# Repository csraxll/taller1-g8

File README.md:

# taller1-g8
Repositorio del proyecto del Grupo 8 para la materia Taller de Proyecto 1 - Ingeniería en Computación - UNLP

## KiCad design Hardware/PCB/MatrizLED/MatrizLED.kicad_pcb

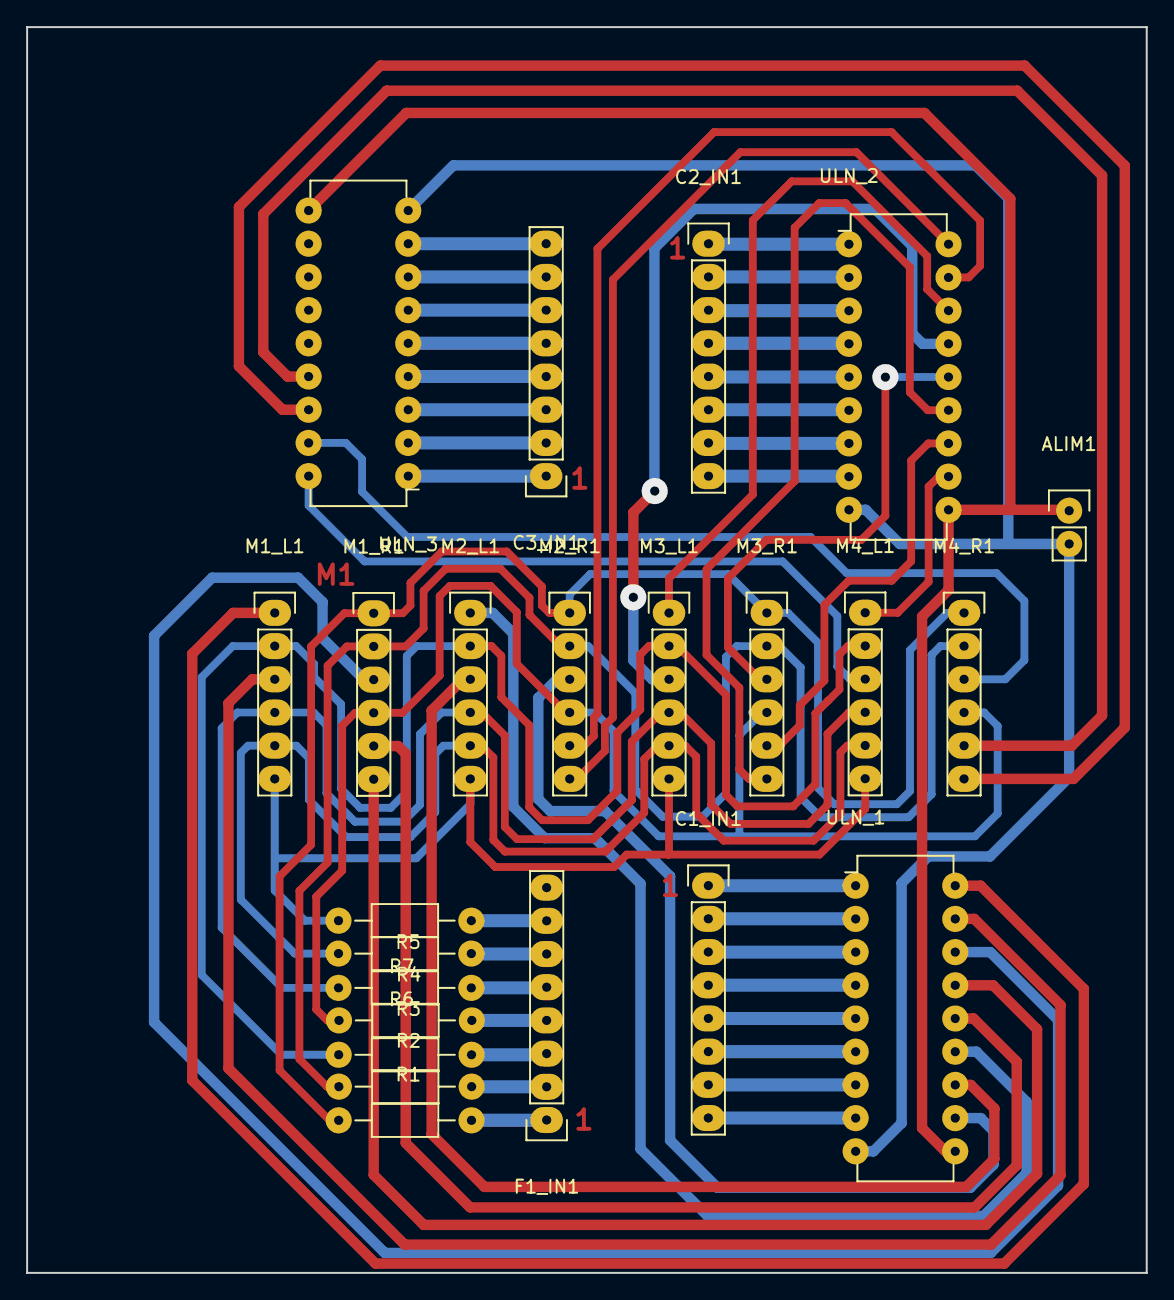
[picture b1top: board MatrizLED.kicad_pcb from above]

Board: 2 copper layers, 85.7 x 95.3 mm, 23 parts (0 on the bottom side), 60 nets.

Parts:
ALIM1: CONN_01X02; Pin_Header_Straight_1x02
C1_IN1, C2_IN1, C3_IN1: CONN_01X08; Pin_Header_Straight_1x08
F1_IN1: CONN_01X08; Pin_Header_Straight_1x08
M1_L1, M1_R1, M2_L1, M2_R1, M3_L1, M3_R1, M4_L1, M4_R1: CONN_01X06; Pin_Header_Straight_1x06
R1, R2, R3, R4, R5, R6, R7: R; Resistor_Horizontal_RM10mm
ULN_1, ULN_2, ULN_3: ULN2803; DIP-18_W7.62mm

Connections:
GND: ALIM1.2, ULN_1.9, ULN_2.9, ULN_3.9
unnamed: C1_IN1.1, ULN_1.1
unnamed: C1_IN1.2, ULN_1.2
unnamed: C1_IN1.3, ULN_1.3
unnamed: C1_IN1.4, ULN_1.4
unnamed: C1_IN1.5, ULN_1.5
unnamed: C1_IN1.6, ULN_1.6
unnamed: C1_IN1.7, ULN_1.7
unnamed: C1_IN1.8, ULN_1.8
unnamed: C2_IN1.1, ULN_2.1
unnamed: C2_IN1.2, ULN_2.2
unnamed: C2_IN1.3, ULN_2.3
unnamed: C2_IN1.4, ULN_2.4
unnamed: C2_IN1.5, ULN_2.5
unnamed: C2_IN1.6, ULN_2.6
unnamed: C2_IN1.7, ULN_2.7
unnamed: C2_IN1.8, ULN_2.8
unnamed: C3_IN1.1, ULN_3.1
unnamed: C3_IN1.2, ULN_3.2
unnamed: C3_IN1.3, ULN_3.3
unnamed: C3_IN1.4, ULN_3.4
unnamed: C3_IN1.5, ULN_3.5
unnamed: C3_IN1.6, ULN_3.6
unnamed: C3_IN1.7, ULN_3.7
unnamed: C3_IN1.8, ULN_3.8
unnamed: F1_IN1.1, R1.2
unnamed: F1_IN1.2, R2.2
unnamed: F1_IN1.3, R3.2
unnamed: F1_IN1.4, R4.2
unnamed: F1_IN1.5, R5.2
unnamed: F1_IN1.6, R6.1
unnamed: F1_IN1.7, R7.1
unnamed: M1_L1.1, ULN_1.18
unnamed: M1_L1.2, M2_L1.2, M3_L1.2, M4_L1.2, R3.1
unnamed: M1_L1.3, ULN_1.17
unnamed: M1_L1.4, M2_L1.4, M3_L1.4, M4_L1.4, R5.1
unnamed: M1_L1.5, M2_L1.5, M3_L1.5, M4_L1.5, R6.2
unnamed: M1_L1.6, M2_L1.6, M3_L1.6, M4_L1.6, R7.2
unnamed: M1_R1.1, M2_R1.1, M3_R1.1, M4_R1.1, R1.1
unnamed: M1_R1.2, M2_R1.2, M3_R1.2, M4_R1.2, R2.1
unnamed: M1_R1.3, ULN_1.16
unnamed: M1_R1.4, M2_R1.4, M3_R1.4, M4_R1.4, R4.1
unnamed: M1_R1.5, ULN_1.14
unnamed: M1_R1.6, ULN_1.15
unnamed: M2_L1.1, ULN_1.13
unnamed: M2_L1.3, ULN_1.12
unnamed: M2_R1.3, ULN_1.11
unnamed: M2_R1.5, ULN_2.17
unnamed: M2_R1.6, ULN_2.18
unnamed: M3_L1.1, ULN_2.16
unnamed: M3_L1.3, ULN_2.15
unnamed: M3_R1.3, ULN_2.14
unnamed: M3_R1.5, ULN_2.12
unnamed: M3_R1.6, ULN_2.13
unnamed: M4_L1.1, ULN_2.11
unnamed: M4_L1.3, ULN_3.18
unnamed: M4_R1.3, ULN_3.17
unnamed: M4_R1.5, ULN_3.15
unnamed: M4_R1.6, ULN_3.16
VCC: ALIM1.1, ULN_1.10, ULN_2.10, ULN_3.10

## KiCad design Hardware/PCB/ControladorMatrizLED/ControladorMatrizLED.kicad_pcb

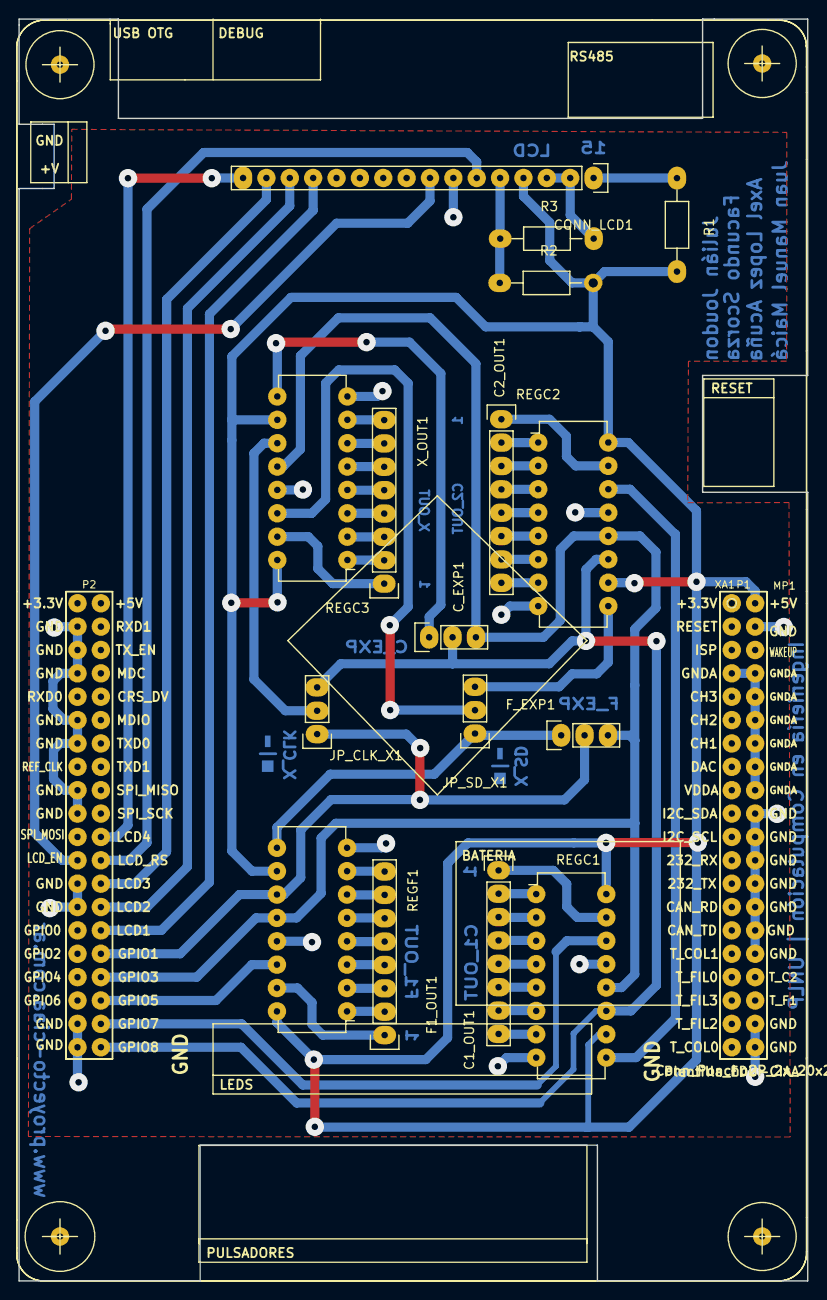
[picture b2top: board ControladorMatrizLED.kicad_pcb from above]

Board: 2 copper layers, 85.7 x 137.2 mm, 18 parts (0 on the bottom side), 54 nets.

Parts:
C1_OUT1, C2_OUT1: CONN_01X08; Socket_Strip_Straight_1x08
CONN_LCD1: CONN_01X16; Socket_Strip_Straight_1x16
C_EXP1: CONN_01X03; Socket_Strip_Straight_1x03
F1_OUT1: CONN_01X08; Socket_Strip_Straight_1x08
F_EXP1: CONN_01X03; Socket_Strip_Straight_1x03
JP_CLK_X1: CONN_01X03; Socket_Strip_Straight_1x03
JP_SD_X1: CONN_01X03; Socket_Strip_Straight_1x03
MP1: Plantilla_EDU-CIAA
R1, R2, R3: R; Resistor_Horizontal_RM10mm
REGC1, REGC2, REGC3: 74HC595; DIP-16_W7.62mm
REGF1: 74HC595; DIP-16_W7.62mm
XA1: Conn_Poncho2P_2x_20x2; poncho_grande
X_OUT1: CONN_01X08; Socket_Strip_Straight_1x08

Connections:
/Circuito Principal/GPIO1: F_EXP1.2, JP_CLK_X1.1, REGF1.11, XA1.72
/Circuito Principal/GPIO3: C_EXP1.3, F_EXP1.3, REGC1.12, REGC2.12, REGC3.12, REGF1.12, XA1.74
/Circuito Principal/GPIO5: REGF1.14, XA1.76
/Circuito Principal/GPIO7: REGC1.14, XA1.78
/Circuito Principal/GPIO8: C_EXP1.2, JP_CLK_X1.3, REGC1.11, REGC2.11, XA1.80
/Circuito Principal/LCD1: CONN_LCD1.13, XA1.70
/Circuito Principal/LCD2: CONN_LCD1.14, XA1.68
/Circuito Principal/LCD3: CONN_LCD1.15, XA1.66
/Circuito Principal/LCD4: CONN_LCD1.16, XA1.62
/Circuito Principal/LCD_EN: CONN_LCD1.8, XA1.63
/Circuito Principal/RS: CONN_LCD1.6, XA1.64
GND: CONN_LCD1.2, CONN_LCD1.3, CONN_LCD1.7, R3.2, REGC1.8, REGC1.13, REGC2.8, REGC2.13, REGC3.8, REGC3.13, REGF1.8, REGF1.13, XA1.4, XA1.20, XA1.22, XA1.24, XA1.26, XA1.28, XA1.30, XA1.32, XA1.38, XA1.40, XA1.43, XA1.45, XA1.47, XA1.51, XA1.53, XA1.57, XA1.59, XA1.65, XA1.67, XA1.77, XA1.79
GNDA: XA1.7, XA1.8, XA1.10, XA1.12, XA1.14, XA1.16, XA1.18
unnamed: C1_OUT1.1, REGC1.15
unnamed: C1_OUT1.2, REGC1.1
unnamed: C1_OUT1.3, REGC1.2
unnamed: C1_OUT1.4, REGC1.3
unnamed: C1_OUT1.5, REGC1.4
unnamed: C1_OUT1.6, REGC1.5
unnamed: C1_OUT1.7, REGC1.6
unnamed: C1_OUT1.8, REGC1.7
unnamed: C2_OUT1.1, REGC2.15
unnamed: C2_OUT1.2, REGC2.1
unnamed: C2_OUT1.3, REGC2.2
unnamed: C2_OUT1.4, REGC2.3
unnamed: C2_OUT1.5, REGC2.4
unnamed: C2_OUT1.6, REGC2.5
unnamed: C2_OUT1.7, REGC2.6
unnamed: C2_OUT1.8, REGC2.7
unnamed: CONN_LCD1.1, R1.1
unnamed: CONN_LCD1.5, R2.1, R3.1
unnamed: C_EXP1.1, REGC3.9
unnamed: F1_OUT1.1, REGF1.15
unnamed: F1_OUT1.2, REGF1.1
unnamed: F1_OUT1.3, REGF1.2
unnamed: F1_OUT1.4, REGF1.3
unnamed: F1_OUT1.5, REGF1.4
unnamed: F1_OUT1.6, REGF1.5
unnamed: F1_OUT1.7, REGF1.6
unnamed: F1_OUT1.8, REGF1.7
unnamed: F_EXP1.1, JP_SD_X1.1, REGF1.9
unnamed: JP_CLK_X1.2, REGC3.11
unnamed: JP_SD_X1.2, REGC3.14
unnamed: JP_SD_X1.3, REGC2.9
unnamed: REGC1.9, REGC2.14
unnamed: REGC3.1, X_OUT1.2
unnamed: REGC3.2, X_OUT1.3
unnamed: REGC3.3, X_OUT1.4
unnamed: REGC3.4, X_OUT1.5
unnamed: REGC3.5, X_OUT1.6
unnamed: REGC3.6, X_OUT1.7
unnamed: REGC3.7, X_OUT1.8
unnamed: REGC3.15, X_OUT1.1
VCC: CONN_LCD1.4, R1.2, R2.2, REGC1.10, REGC1.16, REGC2.10, REGC2.16, REGC3.10, REGC3.16, REGF1.10, REGF1.16, XA1.2

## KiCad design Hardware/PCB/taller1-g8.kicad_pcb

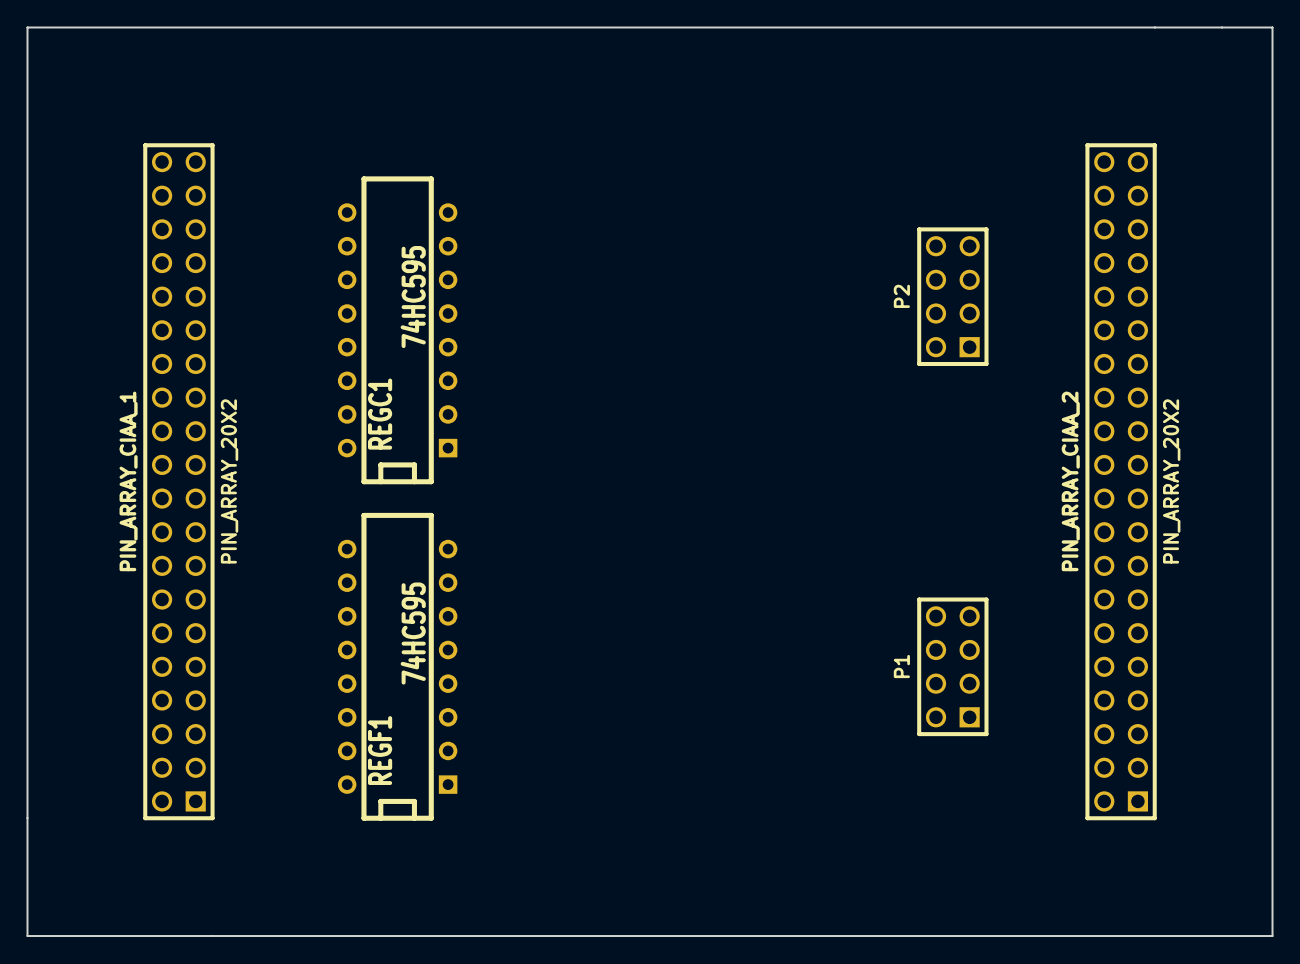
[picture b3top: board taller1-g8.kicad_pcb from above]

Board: 2 copper layers, 94.0 x 68.6 mm, 6 parts (0 on the bottom side), 39 nets, no tracks yet.

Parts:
P1, P2: CONN_8; pin_array_4x2
PIN_ARRAY_CIAA_1, PIN_ARRAY_CIAA_2: PIN_ARRAY_20X2
REGC1: 74HC595; DIP-16__300
REGF1: 74HC595; DIP-16__300

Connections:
/poncho/GPIO2: REGC1.12, REGF1.12
GND: PIN_ARRAY_CIAA_1.2, PIN_ARRAY_CIAA_1.30, PIN_ARRAY_CIAA_1.32, PIN_ARRAY_CIAA_2.2, PIN_ARRAY_CIAA_2.30, PIN_ARRAY_CIAA_2.32, REGC1.8, REGC1.13, REGF1.8, REGF1.13
INT1_1: PIN_ARRAY_CIAA_1.23, PIN_ARRAY_CIAA_2.23
INT2_1: PIN_ARRAY_CIAA_1.24, PIN_ARRAY_CIAA_2.24
unnamed: P2.7, REGC1.6
unnamed: P2.8, REGC1.7
unnamed: P2.1, REGC1.15
unnamed: P1.2, REGF1.1
unnamed: P2.6, REGC1.5
unnamed: P2.5, REGC1.4
unnamed: P2.4, REGC1.3
unnamed: P2.3, REGC1.2
unnamed: P2.2, REGC1.1
unnamed: P1.8, REGF1.7
unnamed: P1.7, REGF1.6
unnamed: P1.6, REGF1.5
unnamed: P1.5, REGF1.4
unnamed: P1.4, REGF1.3
unnamed: P1.3, REGF1.2
unnamed: P1.1, REGF1.15
PA0_1: PIN_ARRAY_CIAA_1.3, PIN_ARRAY_CIAA_2.3
PA1_1: PIN_ARRAY_CIAA_1.4, PIN_ARRAY_CIAA_2.4
PA2_1: PIN_ARRAY_CIAA_1.5, PIN_ARRAY_CIAA_2.5
PA3_1: PIN_ARRAY_CIAA_1.6, PIN_ARRAY_CIAA_2.6
PA4_1: PIN_ARRAY_CIAA_1.7, PIN_ARRAY_CIAA_2.7
PA5_1: PIN_ARRAY_CIAA_1.8, PIN_ARRAY_CIAA_2.8
PA6_1: PIN_ARRAY_CIAA_1.9, PIN_ARRAY_CIAA_2.9
PA7_1: PIN_ARRAY_CIAA_1.10, PIN_ARRAY_CIAA_2.10
PA8_1: PIN_ARRAY_CIAA_1.11, PIN_ARRAY_CIAA_2.11
PA9_1: PIN_ARRAY_CIAA_1.12, PIN_ARRAY_CIAA_2.12
PA10_1: PIN_ARRAY_CIAA_1.13, PIN_ARRAY_CIAA_2.13
PA11_1: PIN_ARRAY_CIAA_1.14, PIN_ARRAY_CIAA_2.14
PA12_1: PIN_ARRAY_CIAA_1.15, PIN_ARRAY_CIAA_2.15
PA13_1: PIN_ARRAY_CIAA_1.16, PIN_ARRAY_CIAA_2.16
PA14_1: PIN_ARRAY_CIAA_1.17, PIN_ARRAY_CIAA_2.17
PA15_1: PIN_ARRAY_CIAA_1.18, PIN_ARRAY_CIAA_1.28, PIN_ARRAY_CIAA_2.18, PIN_ARRAY_CIAA_2.28
PB4_1: PIN_ARRAY_CIAA_1.37, PIN_ARRAY_CIAA_2.37
Tin1_cold_1: PIN_ARRAY_CIAA_1.33, PIN_ARRAY_CIAA_2.33
VCC: PIN_ARRAY_CIAA_1.29, PIN_ARRAY_CIAA_1.31, PIN_ARRAY_CIAA_2.29, PIN_ARRAY_CIAA_2.31, REGC1.10, REGC1.16, REGF1.10, REGF1.16

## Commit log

2015-09-29 Esquemático de la CIAA, el poncho y la matriz de LEDs
2015-09-29 Presentación del Informe Inicial
2015-10-07 Informe Eliminado
2015-10-29 Cambios en los esquematicos y nueva estructura de los directorios
2015-11-12 Programa escrito en C para controlar la matriz de LEDs
2015-11-23 Actualizacion de diseño en PCB utilizando Template del repositorio Ponchos
2015-11-26 Avance sobre Esquematico y PCB - Pistas terminadas
2015-11-29 Pistas completas y prueba de impreso añadida
2015-12-13 Actualizacion con modelo poncho grande y LCD
2016-01-29 Agregados archivos de PCB para la Matriz de LEDs como un añadido al poncho
2016-01-29 Actualizada placa de matrices
2016-02-18 Diseño esquemático y PCB del controlador y del cartel LED
2016-02-18 Programa escrito en C para proveer las funcionalidades del sistema
2016-02-18 Informe inicial del proyecto
2016-02-18 Informe final del proyecto
2016-02-21 Actualizada informacion en doc de archivos de Hardware
2016-02-22 Agregadas hojas de datos de componentes utilizados
2016-02-22 Presentación del informe final del proyecto
